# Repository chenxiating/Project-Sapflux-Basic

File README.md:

# Project-Sapflux-Basic

Hardware designs for simplified PCBs for sapflux monitoring. Designed as a simplified PCB implementation of existing of hand wired designs created by [Xiating Chen](https://github.com/chenxiating) and [Bobby Schulz](https://github.com/bschulz1701).

# Repo Roadmap
<!-- #### [Documents](Documents/)

General document and image storage for repo and README -->

#### [Hardware](Hardware/)

Current board files (Eagle), and other electrical design documents

<!-- #### [Mechanical](Mechanical/)

Mechanical design files and assembly documents -->

#### [Production](Production/)

Contains the various Gerber and pick and place files required to have the Printed Circuit Boards (PCBs) manufactured or populated 

#### [Figures](Figures/)

")
Figure 1: Schematic for wiring the sap flux sensors to a FeatherWing Tripler-compatible board (e.g., a Particle Argon development board).

Figure 2: PCB wiring schematic and finished product for the sensing system.

Figure 3: Urban sap flux sensing system field deployment.

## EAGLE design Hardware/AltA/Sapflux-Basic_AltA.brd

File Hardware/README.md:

## Hardware

Multiple hardware variants of this design were created to leverage flexibility in the design process. Below is a description of the different variants.

#### [Alt - A](AltA/)

<!--  -->
This board is a minor update of the design created by [Xiating Chen](https://github.com/chenxiating) and cleaned up by [Bobby Schulz](https://github.com/bschulz1701). 

#### [Alt - B](AltB/)

This board uses the same component set as [AltA](AltA/) but with an updated layout and some minor features added 

**Changes (vs AltA):**
- Addition of LED on output of heater line
- Updated board dimensions (kept constant for all other variants)
- Cutout and mounting holes for thermocouple amp
- Standard mounting of voltage regulator vs inverted mount on AltA

#### [Alt - C](AltC/)

This board adds support for all feature sets of onboard devices to allow for future firmware development to implement more advanced controls

**Changes (vs AltB):**
- Same mounting layout as AltB
- 9 pin header for thermocouple amp
	- All 4 alert lines from thermocouple amp are connected to feather
- Shutdown line on voltage regulator connected to feather

#### [Alt - D](AltD/)

This board adds all reasonable features while maintaining a simple hand soldered, through hole only design. Major addition here is the added support for soil moisture and rain gauge sensors

**Changes (vs AltC):**
- Same mounting layout as AltC
- Addition of 3 soil moisture sensor inputs 
	- Switchable power rail for soil moisture sensors with a MOSFET switch
	- LED placed on soil moisture power rail 
- Tipping bucket rain gauge connector added

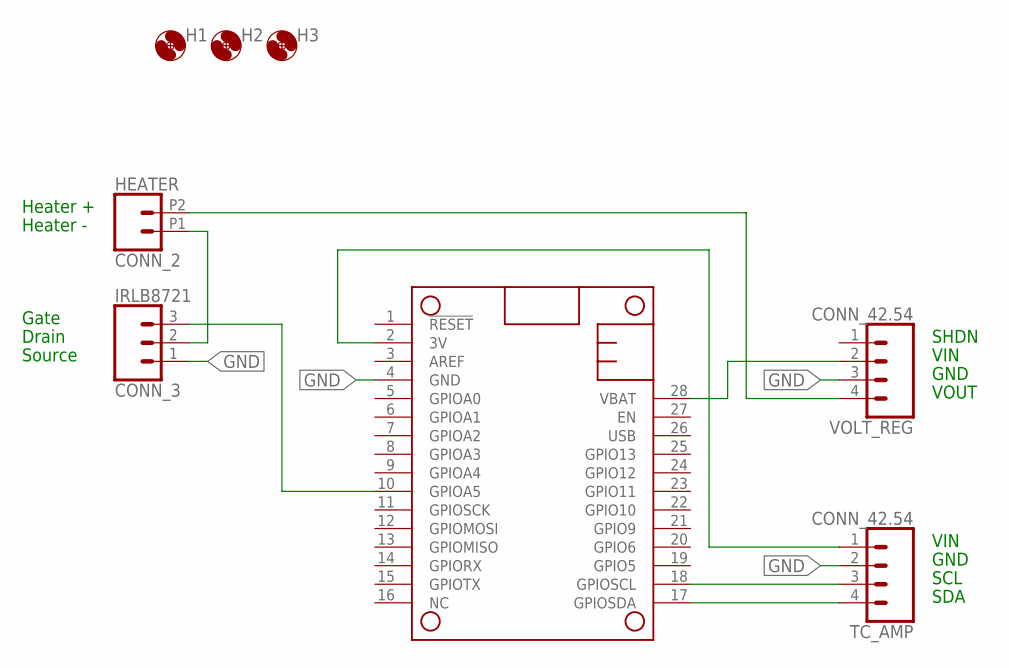
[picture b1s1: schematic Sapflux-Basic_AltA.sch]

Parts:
H1, H2, H3: MOUNTING_HOLE4_NP; 4_40
HEATER: CONN_2; 1X02_2.54_SCREWTERM_ROUND
IRLB8721: CONN_3; 1X03
MS1: FEATHERWINGLAYOUT; FEATHERWING_MIN
TC_AMP: CONN_42.54; 1X04
VOLT_REG: CONN_42.54; 1X04

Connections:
3V: MS1.2 (3V), TC_AMP.1
GND: IRLB8721.1, MS1.4 (GND), TC_AMP.2, VOLT_REG.3
unnamed: MS1.17 (GPIOSDA), TC_AMP.4
unnamed: MS1.18 (GPIOSCL), TC_AMP.3
unnamed: HEATER.P2 (2), VOLT_REG.4
unnamed: HEATER.P1 (1), IRLB8721.2
unnamed: IRLB8721.3, MS1.10 (GPIOA5)
VBAT: MS1.28 (VBAT), VOLT_REG.2

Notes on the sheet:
SHDN
VIN
GND
VOUT
SCL
SDA
Gate
Drain
Source
Heater +
Heater -

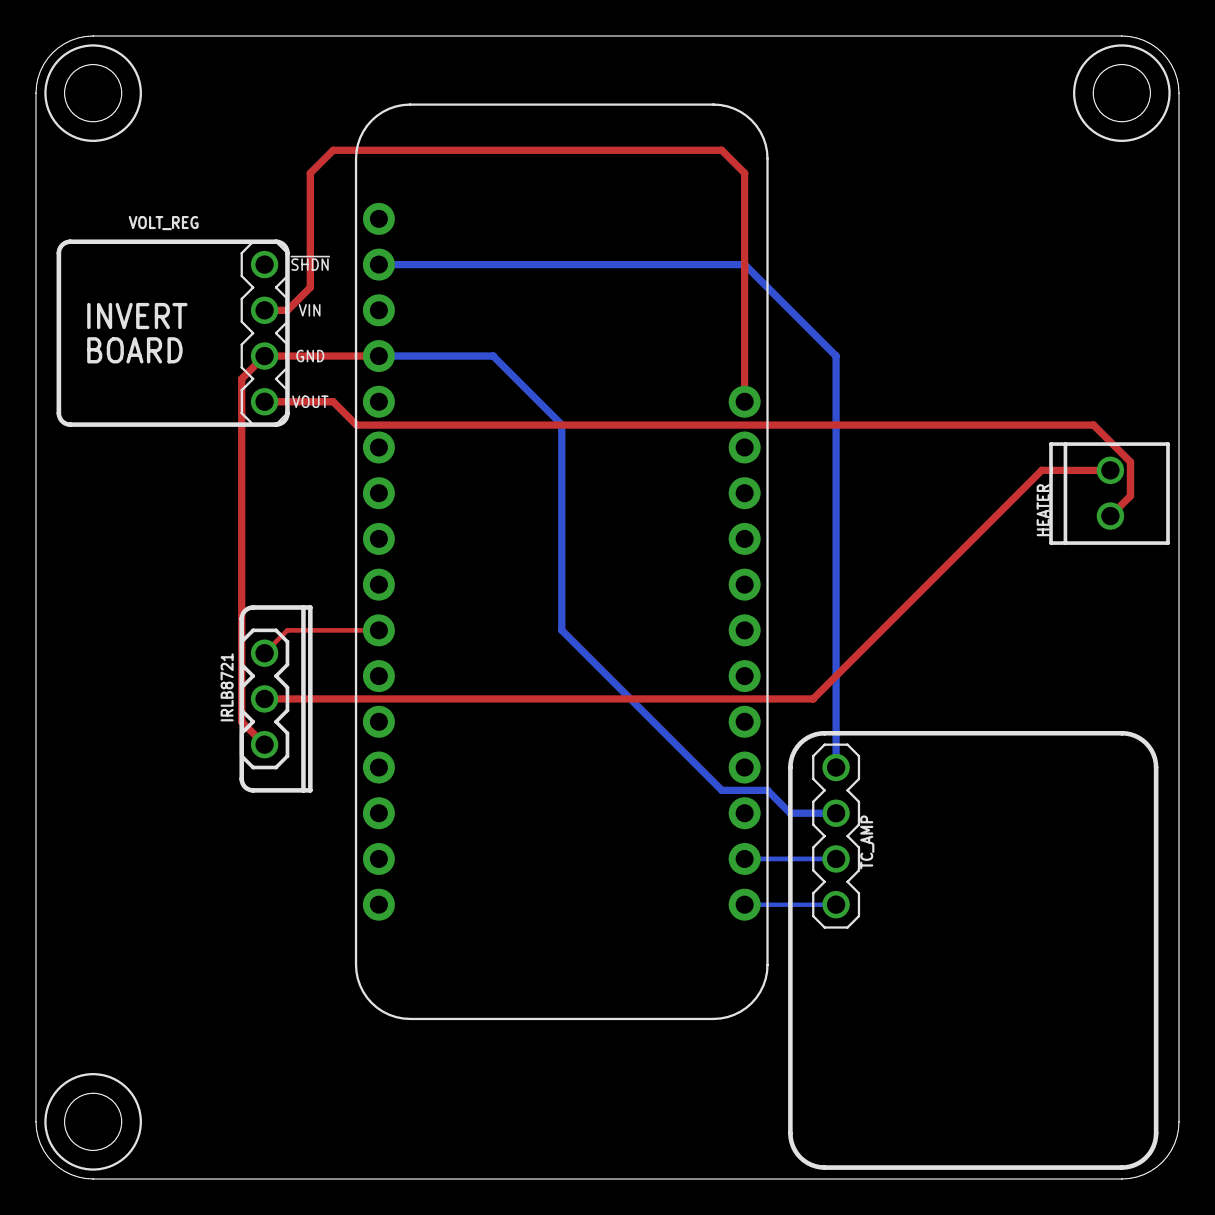
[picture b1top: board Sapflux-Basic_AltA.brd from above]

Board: 2 copper layers, 63.5 x 63.5 mm, 8 parts (0 on the bottom side), 8 nets.

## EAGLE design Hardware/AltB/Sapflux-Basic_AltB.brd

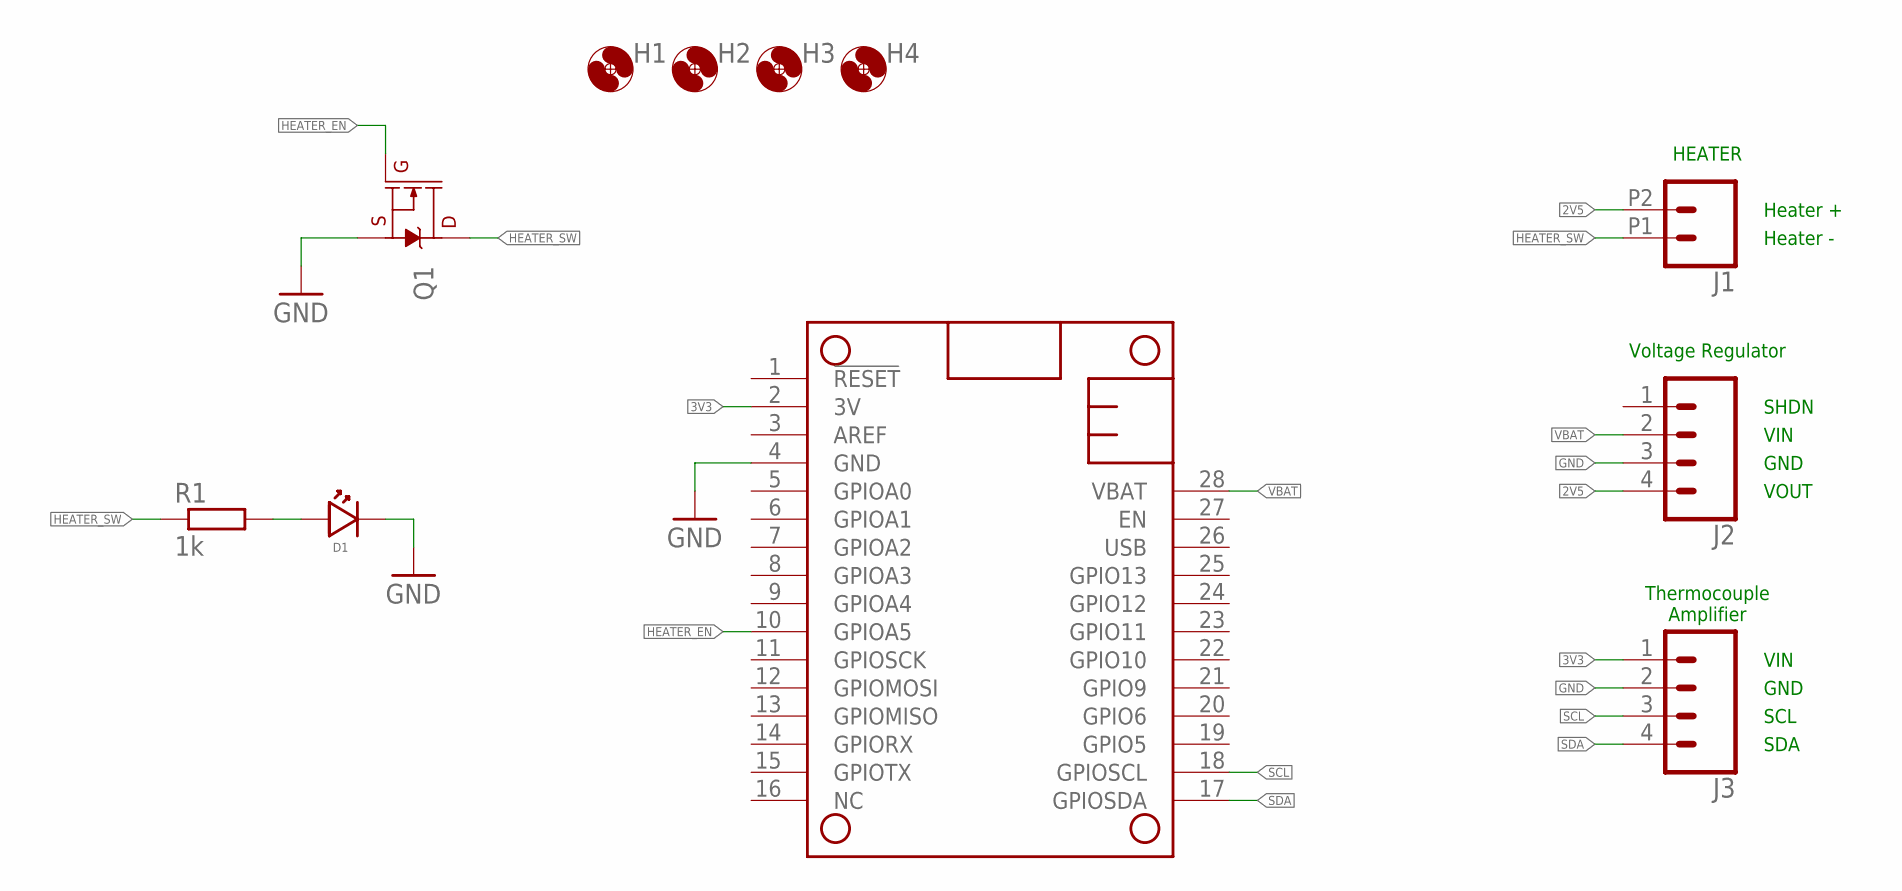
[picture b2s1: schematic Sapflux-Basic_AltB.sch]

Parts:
D1: LED3MM; LED_3MM
H1, H2, H3, H4: MOUNTING_HOLE4_NP; 4_40
J1: CONN_2; 1X02_2.54_SCREWTERM_ROUND
J2, J3: CONN_42.54; 1X04; MPN PH1-04-UA; DIGIKEY 2057-PH1-04-UA-ND
MS1: FEATHERWINGLAYOUT; FEATHERWING_MIN
Q1: 60V/32A/35mΩ; TO220V; MPN IRLB8721PBF; DIGIKEY IRLB8721PBF-ND
R1: 1k; 0204/7

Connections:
2V5: J1.P2 (2), J2.4
3V3: J3.1, MS1.2 (3V)
GND: D1.2 (CATHODE), J2.3, J3.2, MS1.4 (GND), Q1.3 (S)
HEATER_EN: MS1.10 (GPIOA5), Q1.1 (G)
HEATER_SW: J1.P1 (1), Q1.2 (D), R1.1
unnamed: D1.1 (ANODE), R1.2
SCL: J3.3, MS1.18 (GPIOSCL)
SDA: J3.4, MS1.17 (GPIOSDA)
VBAT: J2.2, MS1.28 (VBAT)

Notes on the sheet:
SHDN
VIN
GND
VOUT
SCL
SDA
Heater +
Heater -
HEATER
Voltage Regulator
Thermocouple Amplifier

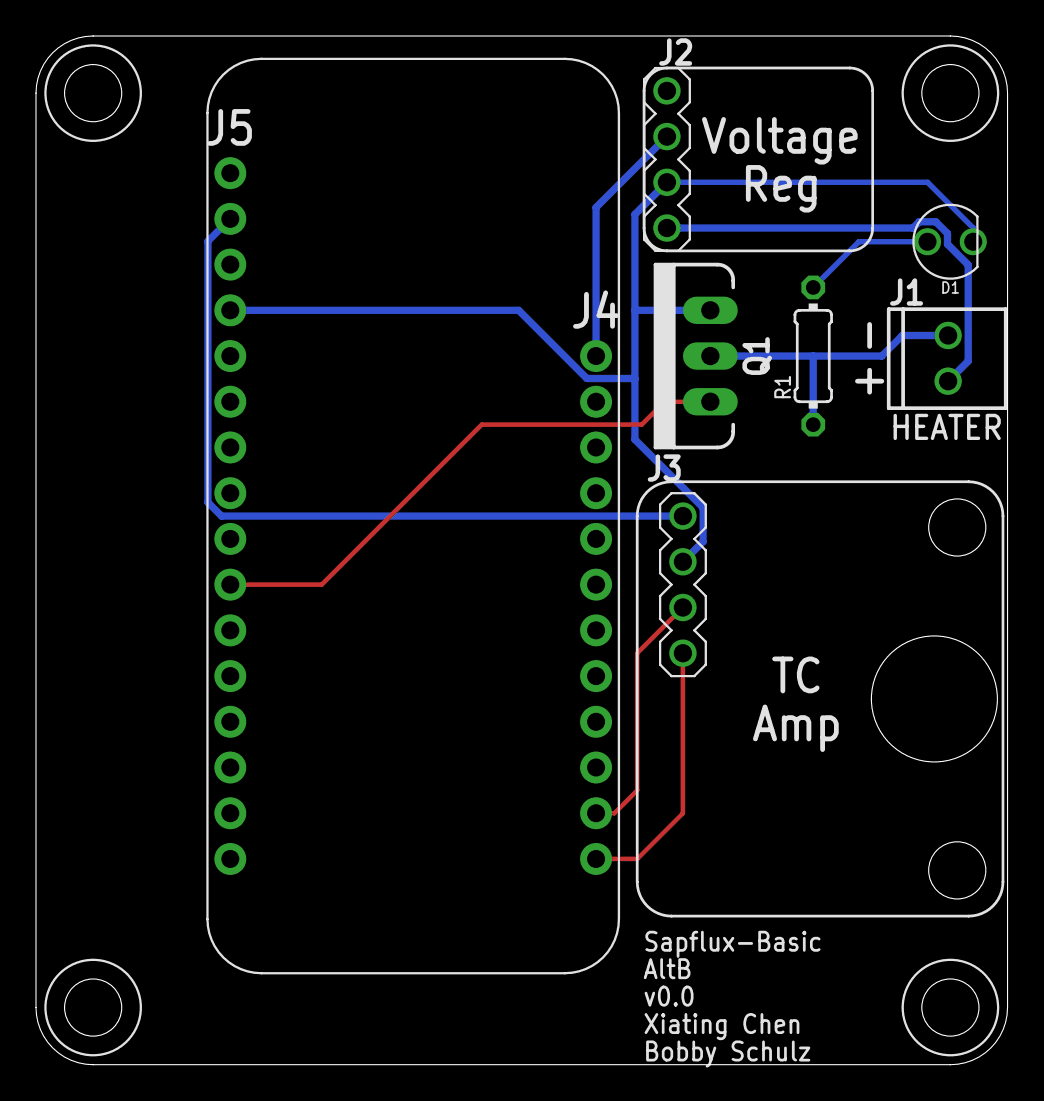
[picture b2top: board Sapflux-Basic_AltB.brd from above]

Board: 2 copper layers, 54.0 x 57.1 mm, 11 parts (0 on the bottom side), 9 nets.

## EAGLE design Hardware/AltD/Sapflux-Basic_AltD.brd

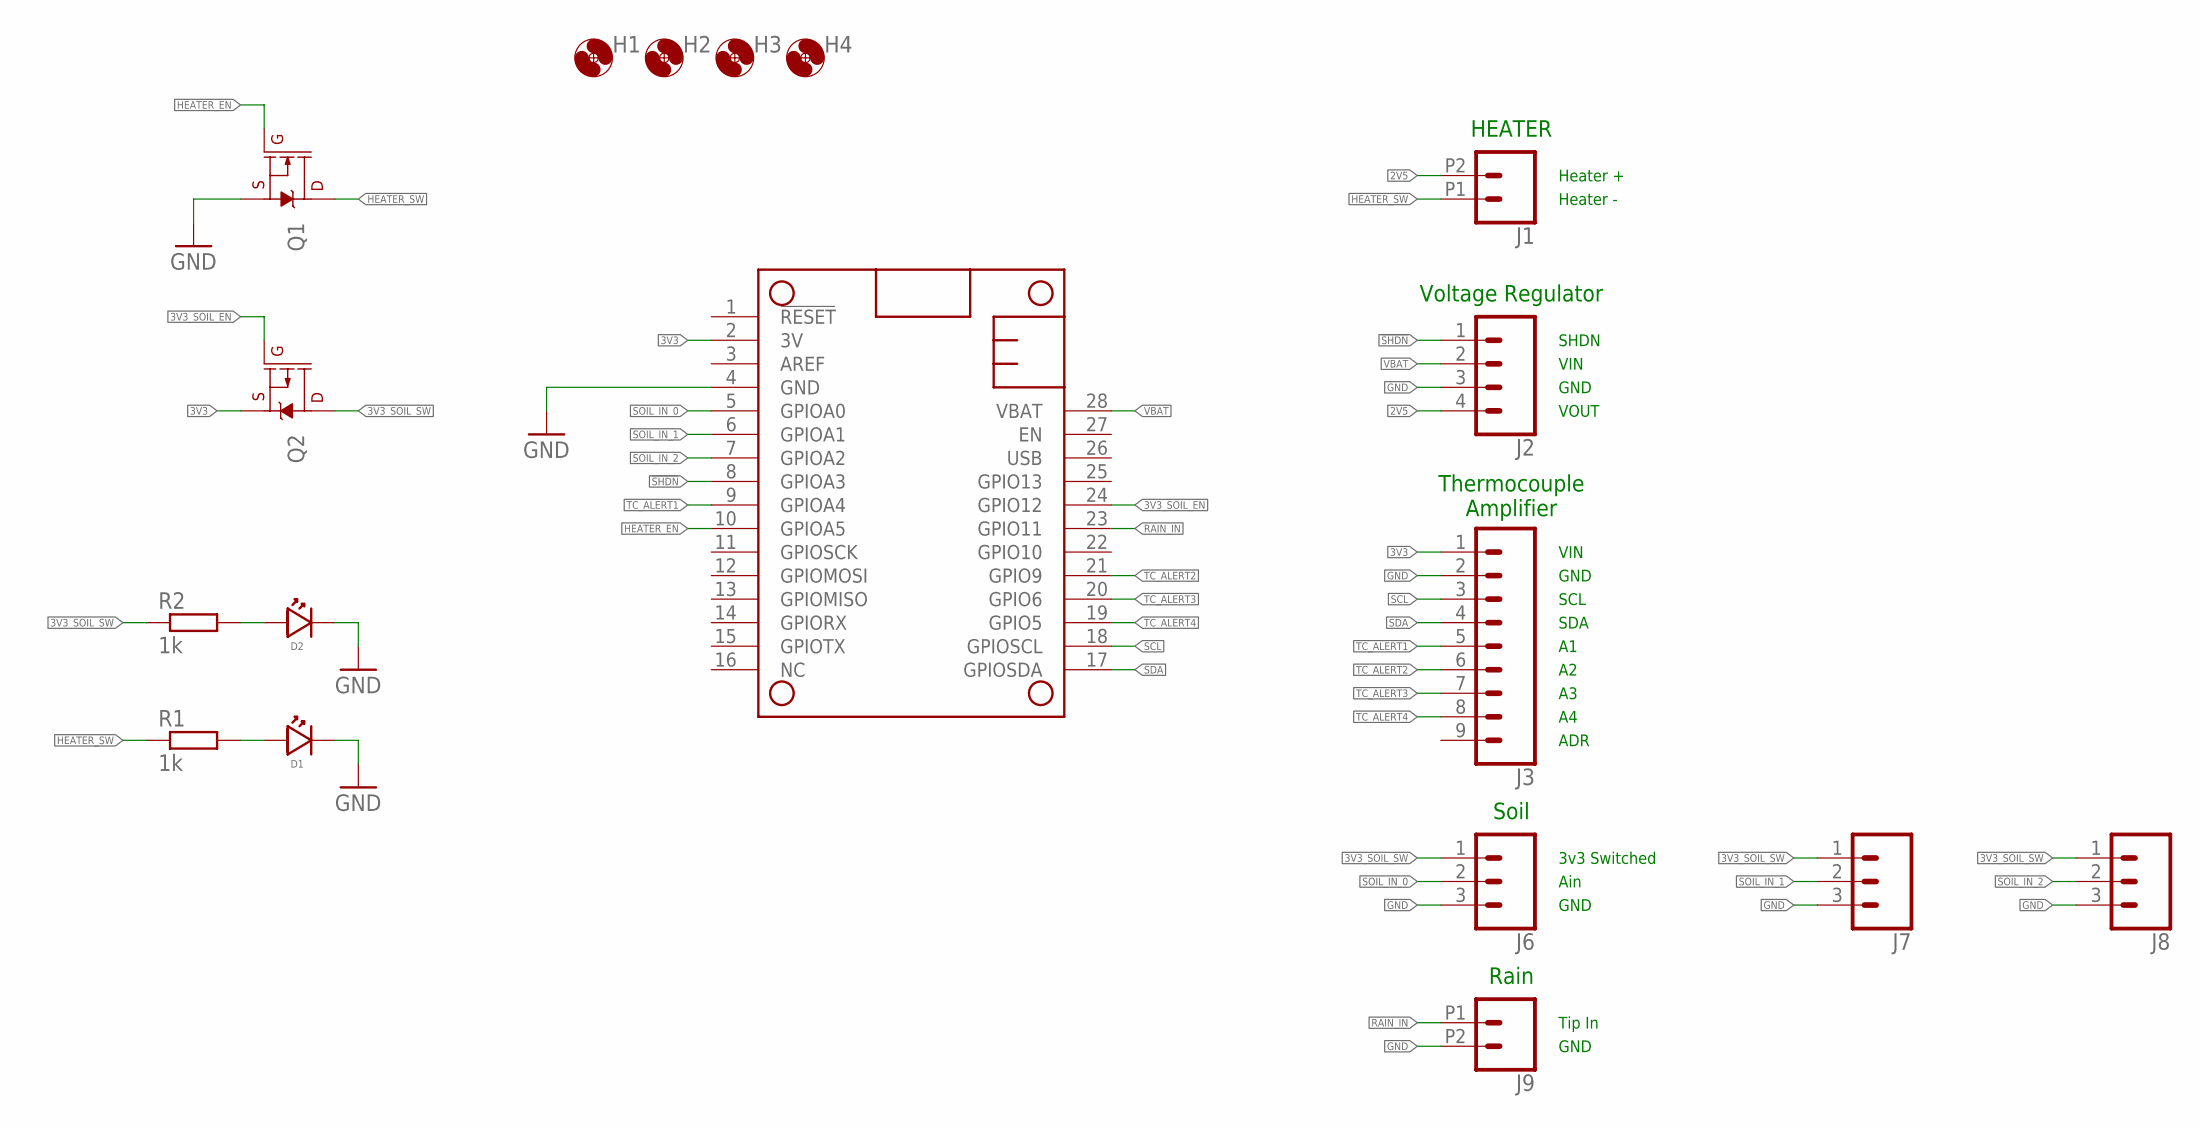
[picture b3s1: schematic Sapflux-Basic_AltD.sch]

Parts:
D1, D2: LED3MM; LED_3MM
H1, H2, H3, H4: MOUNTING_HOLE4_NP; 4_40
J1: CONN_2; 1X02_2.54_SCREWTERM_ROUND
J2: CONN_42.54; 1X04; MPN PH1-04-UA; DIGIKEY 2057-PH1-04-UA-ND
J3: CONN_9; 1X09; MPN PH1-09-UA; DIGIKEY 2057-PH1-09-UA-ND
J6, J7, J8: CONN_32.54_SCREW; 1X03_SCREW
J9: CONN_022.54_SCREW_ROUND; 1X02_2.54_SCREWTERM_ROUND
MS1: FEATHERWINGLAYOUT; FEATHERWING_MIN
Q1: 60V/32A/35mΩ; TO220V; MPN IRLB8721PBF; DIGIKEY IRLB8721PBF-ND
Q2: 24A/20V/50mΩ; TO220V; MPN SUP53P06-20-E3; DIGIKEY SUP53P06-20-E3-ND
R1, R2: 1k; 0204/7

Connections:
2V5: J1.P2 (2), J2.4
3V3: J3.1, MS1.2 (3V), Q2.3 (S)
3V3_SOIL_EN: MS1.24 (GPIO12), Q2.1 (G)
3V3_SOIL_SW: J6.1, J7.1, J8.1, Q2.2 (D), R2.1
!SHDN: J2.1, MS1.8 (GPIOA3)
GND: D1.2 (CATHODE), D2.2 (CATHODE), J2.3, J3.2, J6.3, J7.3, J8.3, J9.P2 (2), MS1.4 (GND), Q1.3 (S)
HEATER_EN: MS1.10 (GPIOA5), Q1.1 (G)
HEATER_SW: J1.P1 (1), Q1.2 (D), R1.1
unnamed: D2.1 (ANODE), R2.2
unnamed: D1.1 (ANODE), R1.2
RAIN_IN: J9.P1 (1), MS1.23 (GPIO11)
SCL: J3.3, MS1.18 (GPIOSCL)
SDA: J3.4, MS1.17 (GPIOSDA)
SOIL_IN_0: J6.2, MS1.5 (GPIOA0)
SOIL_IN_1: J7.2, MS1.6 (GPIOA1)
SOIL_IN_2: J8.2, MS1.7 (GPIOA2)
TC_ALERT1: J3.5, MS1.9 (GPIOA4)
TC_ALERT2: J3.6, MS1.21 (GPIO9)
TC_ALERT3: J3.7, MS1.20 (GPIO6)
TC_ALERT4: J3.8, MS1.19 (GPIO5)
VBAT: J2.2, MS1.28 (VBAT)

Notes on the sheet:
SHDN
VIN
GND
VOUT
SCL
SDA
Heater +
Heater -
HEATER
Voltage Regulator
Thermocouple Amplifier
ADR
Rain
Soil
Ain
3v3 Switched
Tip In

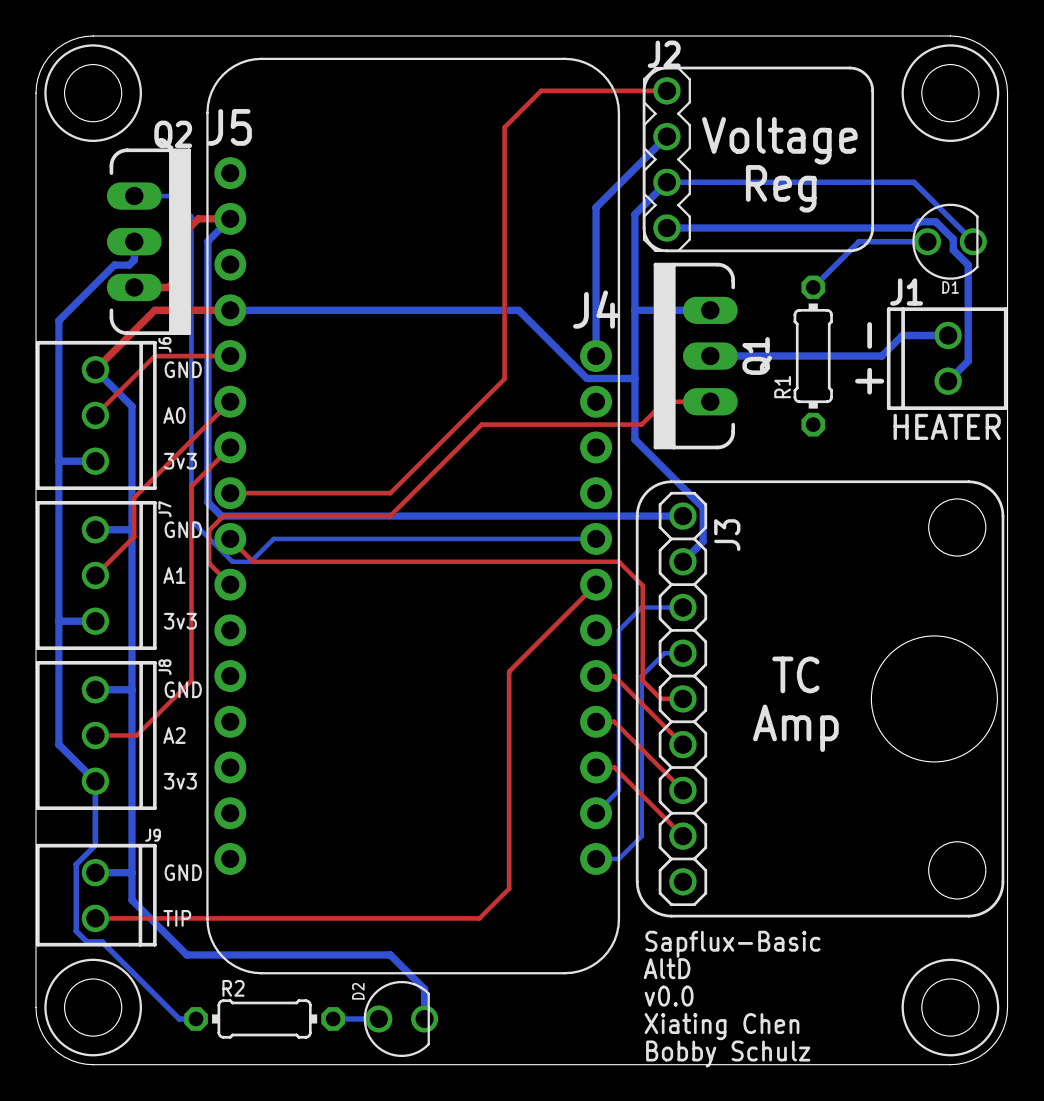
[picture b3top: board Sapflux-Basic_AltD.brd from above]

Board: 2 copper layers, 54.0 x 57.1 mm, 18 parts (0 on the bottom side), 21 nets.

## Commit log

2024-11-26 Added CC license

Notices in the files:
parts and their libraries:
SparkFun-DiscreteSemi: Licensing: Creative Commons ShareAlike 4.0 International - https://creativecommons.org/licenses/by-sa/4.0
bschulz: This work is licensed under the Creative Commons Attribution-ShareAlike 4.0
http://creativecommons.org/licenses/by-sa/4.0
